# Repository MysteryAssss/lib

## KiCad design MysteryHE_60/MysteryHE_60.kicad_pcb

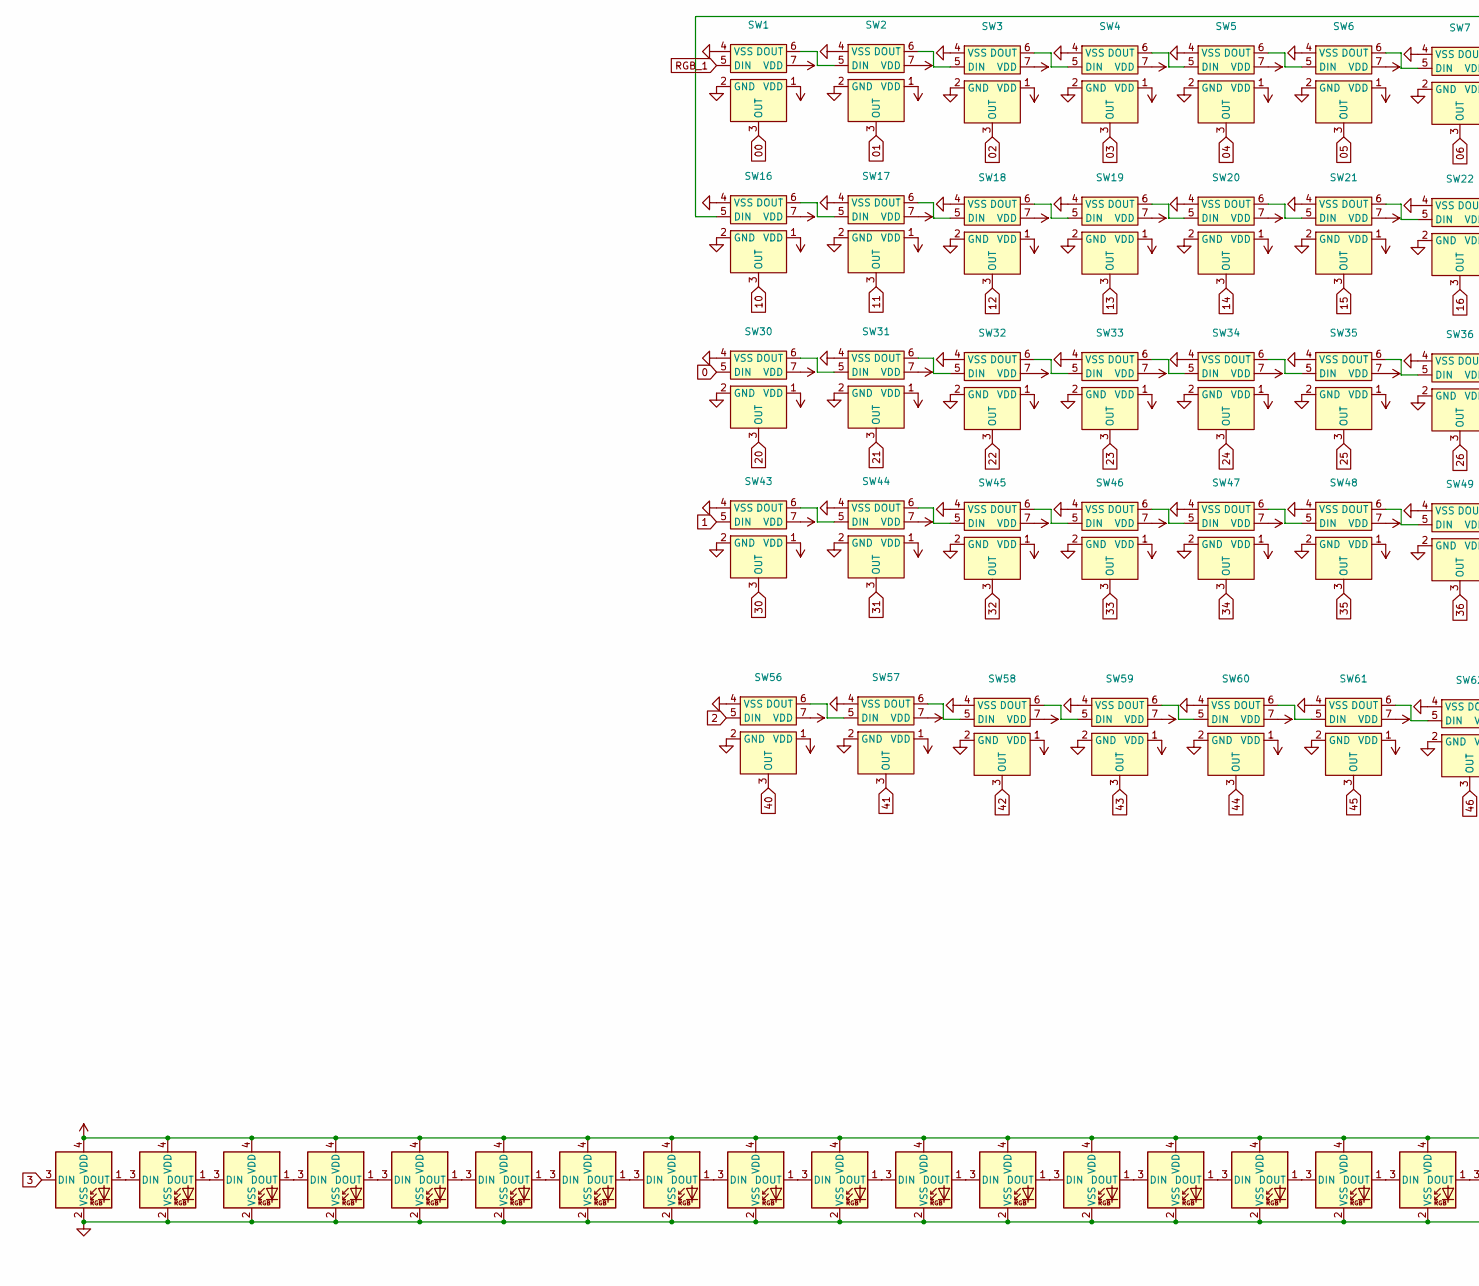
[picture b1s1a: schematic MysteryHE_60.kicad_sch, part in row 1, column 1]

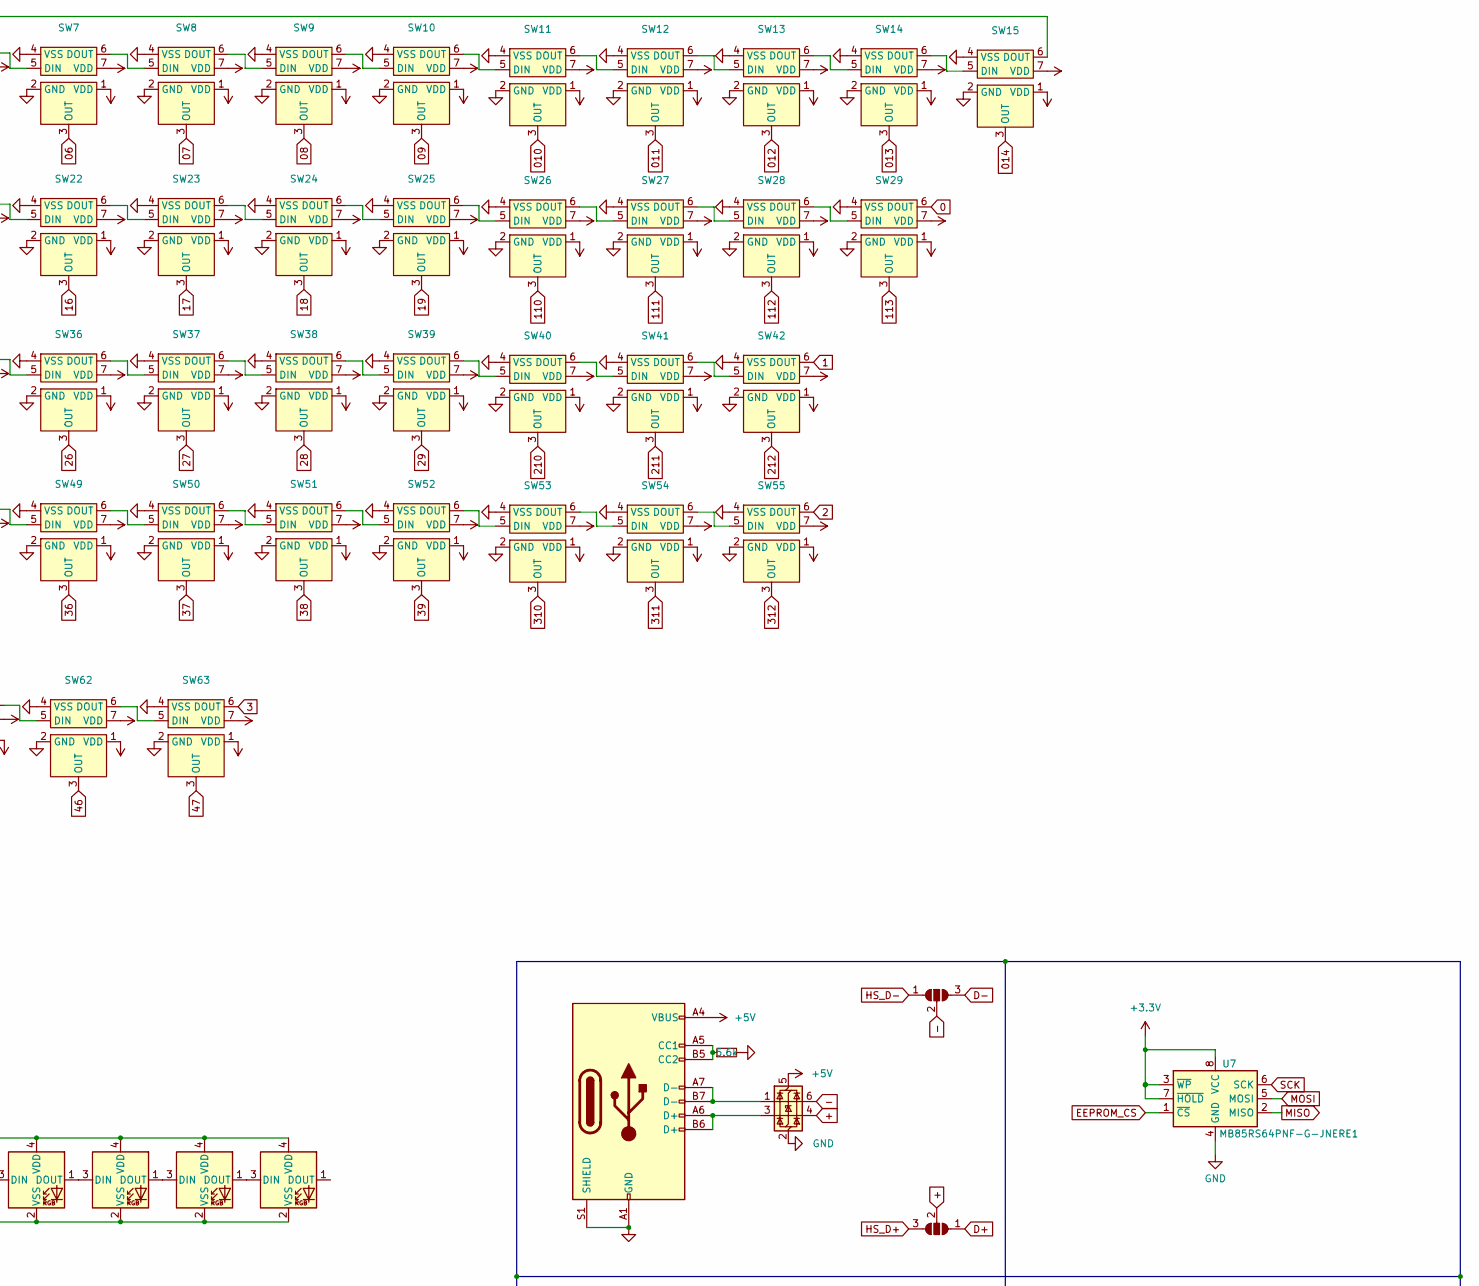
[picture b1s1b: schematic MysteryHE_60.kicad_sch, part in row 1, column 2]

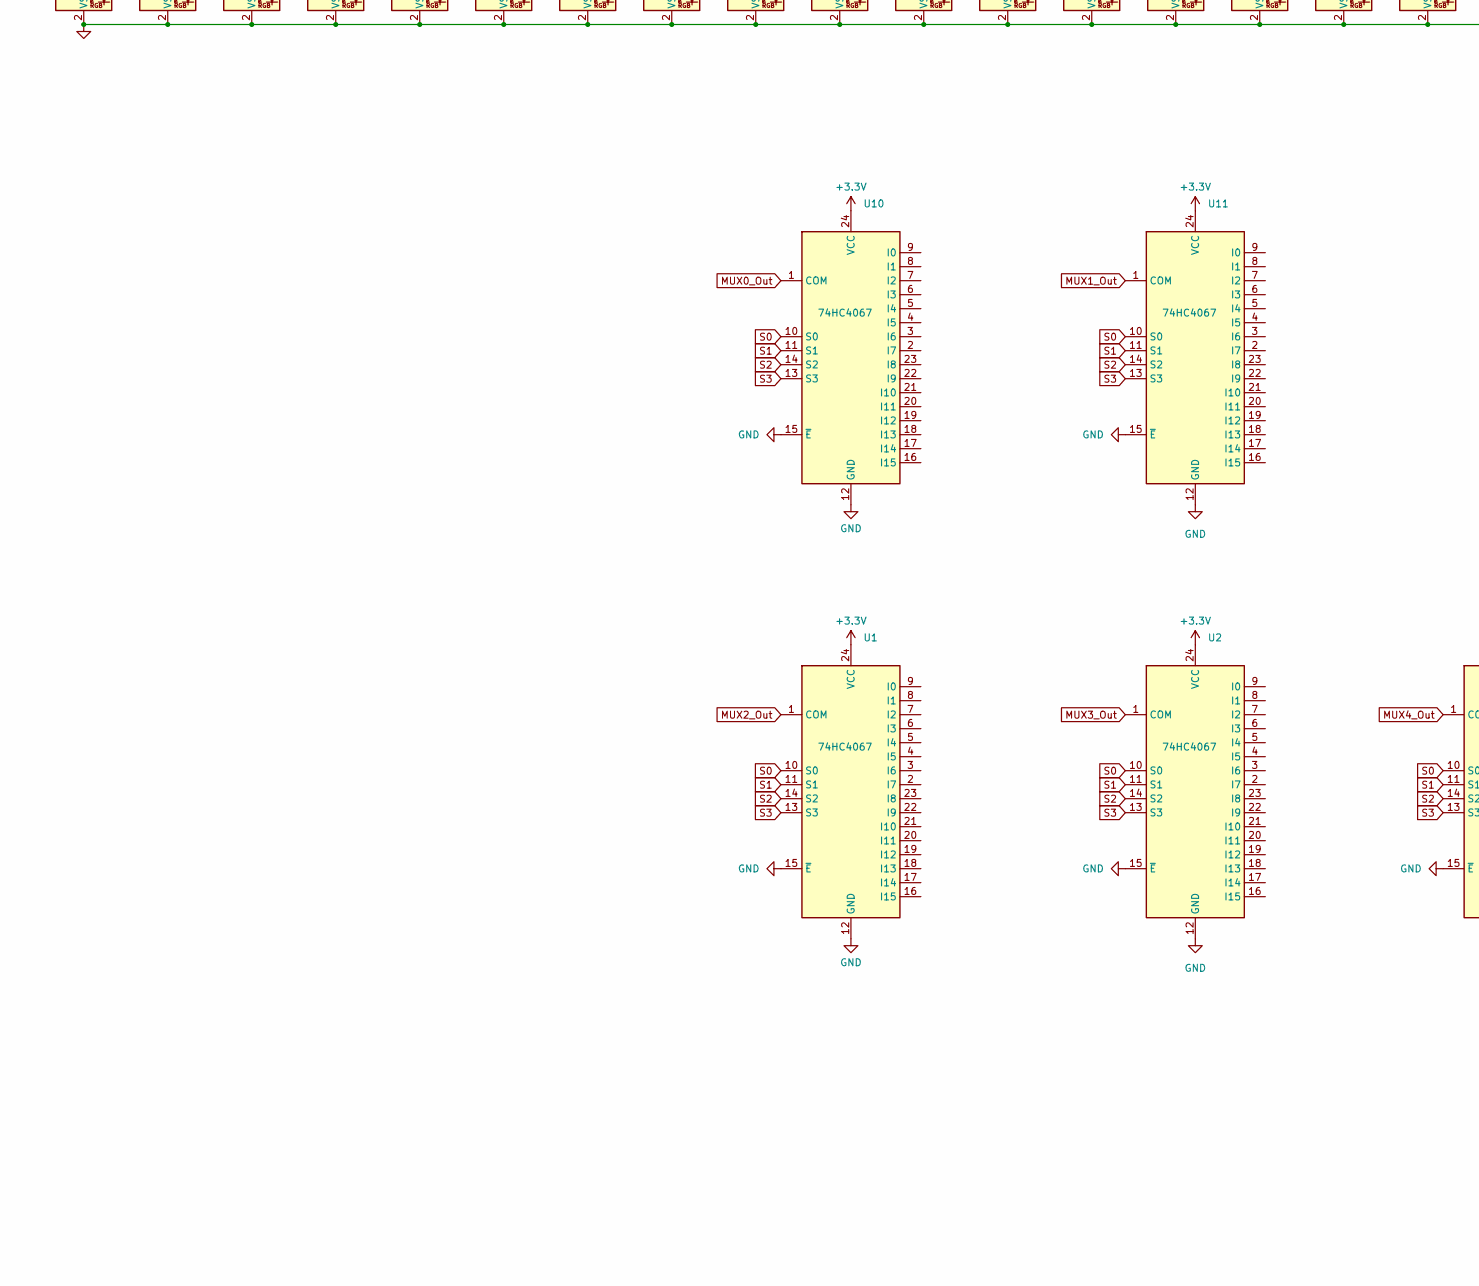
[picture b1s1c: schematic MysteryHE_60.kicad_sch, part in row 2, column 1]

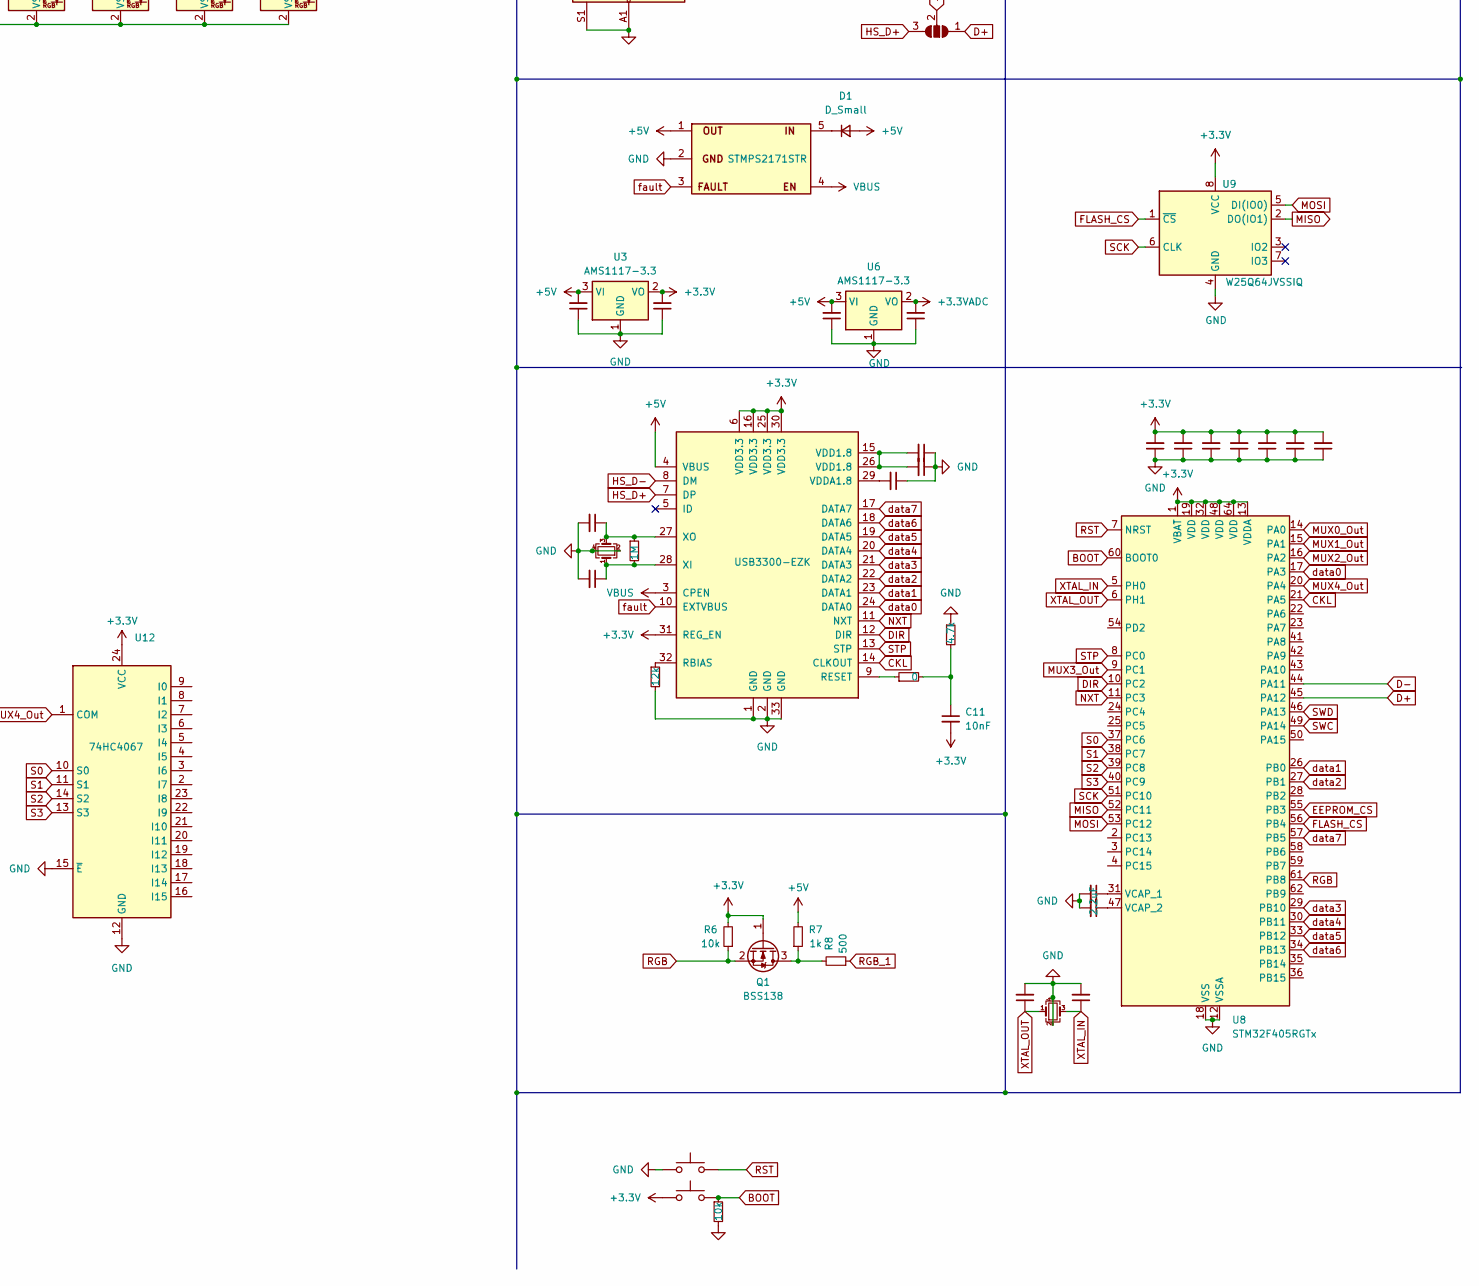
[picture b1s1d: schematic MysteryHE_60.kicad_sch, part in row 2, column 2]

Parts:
BOOT1: SW_Push; JST_EH_B2B-EH-A_1x02_P2.50mm_Vertical
C1, C2, C3, C5, C6, C8, C12, C15: 12pF; C_0603_1608Metric
C7, C9: 4.7uF; C_0603_1608Metric
C10: 1uF; C_0603_1608Metric
C11: 10nF; C_0603_1608Metric
C16, C17: 2.2uF; C_0603_1608Metric
C18, C19, C20, C21, C22, C23, C24: 0.1Uf; C_0603_1608Metric
D1: D_Small; D_SOD-123
Drgb1, Drgb2, Drgb3, Drgb4, Drgb5, Drgb6, Drgb7, Drgb8, Drgb9, Drgb10, Drgb11, Drgb12, Drgb13, Drgb14, Drgb15, Drgb16, Drgb17, Drgb18, Drgb19, Drgb20: WS2812B-2020; LED_WS2812B-2020_PLCC4_2.0x2.0mm
J1: STMPS2171STR; SOT-23-5
JP1, JP2: SolderJumper_3_Open; SW_SPDT_PCM12
Jd1: USB_C_Receptacle_USB2.0_14P; USB_C_Receptacle_G-Switch_GT-USB-7010ASV
Q1: BSS138; SOT-23
R1: 1M; R_0603_1608Metric
R3: 12k; R_0603_1608Metric
R4, R6: 10k; R_0603_1608Metric
R5: 5.6k; R_0603_1608Metric
R7: 1k; R_0603_1608Metric
R8: 500; R_0603_1608Metric
R9: 0; R_0603_1608Metric
R10: 4.7k; R_0603_1608Metric
RST1: SW_Push; JST_EH_B2B-EH-A_1x02_P2.50mm_Vertical
SW1, SW2, SW3, SW4, SW5, SW6, SW7, SW8, SW9, SW10, SW11, SW12, SW13, SW14, SW15, SW17, SW18, SW19, SW20, SW21, SW22, SW23, SW24, SW25, SW26, SW27, SW28, SW31, SW32, SW33, SW34, SW35, SW36, SW37, SW38, SW39, SW40, SW41, SW44, SW45, SW46, SW47, SW48, SW49, SW50, SW51, SW52, SW53, SW55, SW57, SW61: HE_1u RGB
SW16, SW29, SW56, SW58, SW60, SW62: HE_1.5u RGB
SW30, SW54: HE_1.75u RGB
SW42, SW43: HE_2.25u RGB
SW59: HE_7u Reversed RGB
SW63: HE_2u RGB
U1, U2, U10, U11, U12: 74HC4067; TSSOP-24_4.4x7.8mm_P0.65mm
U3, U6: AMS1117-3.3; SOT-223-3_TabPin2
U4: USB3300-EZK; QFN-32-1EP_5x5mm_P0.5mm_EP3.45x3.45mm
U5: USBLC6-2SC6; SOT-23-6
U7: MB85RS64PNF-G-JNERE1; SO-8_3.9x4.9mm_P1.27mm; LCSC C8741
U8: STM32F405RGTx; LQFP-64_10x10mm_P0.5mm
U9: W25Q64JVSSIQ; SOIC-8_5.23x5.23mm_P1.27mm; LCSC C179171
Y1: 24mhz; Crystal_SMD_3225-4Pin_3.2x2.5mm
Y2: 12mhz; Crystal_SMD_3225-4Pin_3.2x2.5mm

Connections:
0: SW29.6 (DOUT), SW30.5 (DIN)
00: SW1.3 (OUT)
1: SW42.6 (DOUT), SW43.5 (DIN)
01: SW2.3 (OUT)
02: SW3.3 (OUT)
2: SW55.6 (DOUT), SW56.5 (DIN)
3: Drgb20.3 (DIN), SW63.6 (DOUT)
03: SW4.3 (OUT)
04: SW5.3 (OUT)
05: SW6.3 (OUT)
06: SW7.3 (OUT)
07: SW8.3 (OUT)
08: SW9.3 (OUT)
09: SW10.3 (OUT)
10: SW16.3 (OUT)
010: SW11.3 (OUT)
011: SW12.3 (OUT)
11: SW17.3 (OUT)
012: SW13.3 (OUT)
12: SW18.3 (OUT)
013: SW14.3 (OUT)
13: SW19.3 (OUT)
14: SW20.3 (OUT)
014: SW15.3 (OUT)
15: SW21.3 (OUT)
16: SW22.3 (OUT)
17: SW23.3 (OUT)
18: SW24.3 (OUT)
19: SW25.3 (OUT)
20: SW30.3 (OUT)
21: SW31.3 (OUT)
22: SW32.3 (OUT)
23: SW33.3 (OUT)
24: SW34.3 (OUT)
25: SW35.3 (OUT)
26: SW36.3 (OUT)
27: SW37.3 (OUT)
28: SW38.3 (OUT)
29: SW39.3 (OUT)
30: SW43.3 (OUT)
31: SW44.3 (OUT)
32: SW45.3 (OUT)
33: SW46.3 (OUT)
34: SW47.3 (OUT)
35: SW48.3 (OUT)
36: SW49.3 (OUT)
37: SW50.3 (OUT)
38: SW51.3 (OUT)
39: SW52.3 (OUT)
40: SW56.3 (OUT)
41: SW57.3 (OUT)
42: SW58.3 (OUT)
43: SW59.3 (OUT)
44: SW60.3 (OUT)
45: SW61.3 (OUT)
46: SW62.3 (OUT)
47: SW63.3 (OUT)
110: SW26.3 (OUT)
111: SW27.3 (OUT)
112: SW28.3 (OUT)
113: SW29.3 (OUT)
210: SW40.3 (OUT)
211: SW41.3 (OUT)
212: SW42.3 (OUT)
310: SW53.3 (OUT)
311: SW54.3 (OUT)
312: SW55.3 (OUT)
+: JP2.2 (C), U5.4 (I/O2)
+3.3V: BOOT1.1, C5.2, C11.2, C18.2, C19.2, C20.2, C21.2, C22.2, C23.2, C24.2, Q1.1 (G), R6.2, U1.24 (VCC), U2.24 (VCC), U3.2 (VO), U4.6 (VDD3.3), U4.16 (VDD3.3), U4.25 (VDD3.3), U4.30 (VDD3.3), U4.31 (REG_EN), U7.3 (~WP), U7.7 (~HOLD), U7.8 (VCC), U8.1 (VBAT), U8.13 (VDDA), U8.19 (VDD), U8.32 (VDD), U8.48 (VDD), U8.64 (VDD), U9.8 (VCC), U10.24 (VCC), U11.24 (VCC), U12.24 (VCC)
+3.3VADC: C8.2, SW1.1 (VDD), SW2.1 (VDD), SW3.1 (VDD), SW4.1 (VDD), SW5.1 (VDD), SW6.1 (VDD), SW7.1 (VDD), SW8.1 (VDD), SW9.1 (VDD), SW10.1 (VDD), SW11.1 (VDD), SW12.1 (VDD), SW13.1 (VDD), SW14.1 (VDD), SW15.1 (VDD), SW16.1 (VDD), SW17.1 (VDD), SW18.1 (VDD), SW19.1 (VDD), SW20.1 (VDD), SW21.1 (VDD), SW22.1 (VDD), SW23.1 (VDD), SW24.1 (VDD), SW25.1 (VDD), SW26.1 (VDD), SW27.1 (VDD), SW28.1 (VDD), SW29.1 (VDD), SW30.1 (VDD), SW31.1 (VDD), SW32.1 (VDD), SW33.1 (VDD), SW34.1 (VDD), SW35.1 (VDD), SW36.1 (VDD), SW37.1 (VDD), SW38.1 (VDD), SW39.1 (VDD), SW40.1 (VDD), SW41.1 (VDD), SW42.1 (VDD), SW43.1 (VDD), SW44.1 (VDD), SW45.1 (VDD), SW46.1 (VDD), SW47.1 (VDD), SW48.1 (VDD), SW49.1 (VDD), SW50.1 (VDD), SW51.1 (VDD), SW52.1 (VDD), SW53.1 (VDD), SW54.1 (VDD), SW55.1 (VDD), SW56.1 (VDD), SW57.1 (VDD), SW58.1 (VDD), SW59.1 (VDD), SW60.1 (VDD), SW61.1 (VDD), SW62.1 (VDD), SW63.1 (VDD), U6.2 (VO)
+5V: C1.2, C6.2, D1.2 (A), Drgb1.4 (VDD), Drgb2.4 (VDD), Drgb3.4 (VDD), Drgb4.4 (VDD), Drgb5.4 (VDD), Drgb6.4 (VDD), Drgb7.4 (VDD), Drgb8.4 (VDD), Drgb9.4 (VDD), Drgb10.4 (VDD), Drgb11.4 (VDD), Drgb12.4 (VDD), Drgb13.4 (VDD), Drgb14.4 (VDD), Drgb15.4 (VDD), Drgb16.4 (VDD), Drgb17.4 (VDD), Drgb18.4 (VDD), Drgb19.4 (VDD), Drgb20.4 (VDD), J1.1, Jd1.A4 (VBUS), Jd1.A9 (VBUS), Jd1.B4 (VBUS), Jd1.B9 (VBUS), R7.2, SW1.7 (VDD), SW2.7 (VDD), SW3.7 (VDD), SW4.7 (VDD), SW5.7 (VDD), SW6.7 (VDD), SW7.7 (VDD), SW8.7 (VDD), SW9.7 (VDD), SW10.7 (VDD), SW11.7 (VDD), SW12.7 (VDD), SW13.7 (VDD), SW14.7 (VDD), SW15.7 (VDD), SW16.7 (VDD), SW17.7 (VDD), SW18.7 (VDD), SW19.7 (VDD), SW20.7 (VDD), SW21.7 (VDD), SW22.7 (VDD), SW23.7 (VDD), SW24.7 (VDD), SW25.7 (VDD), SW26.7 (VDD), SW27.7 (VDD), SW28.7 (VDD), SW29.7 (VDD), SW30.7 (VDD), SW31.7 (VDD), SW32.7 (VDD), SW33.7 (VDD), SW34.7 (VDD), SW35.7 (VDD), SW36.7 (VDD), SW37.7 (VDD), SW38.7 (VDD), SW39.7 (VDD), SW40.7 (VDD), SW41.7 (VDD), SW42.7 (VDD), SW43.7 (VDD), SW44.7 (VDD), SW45.7 (VDD), SW46.7 (VDD), SW47.7 (VDD), SW48.7 (VDD), SW49.7 (VDD), SW50.7 (VDD), SW51.7 (VDD), SW52.7 (VDD), SW53.7 (VDD), SW54.7 (VDD), SW55.7 (VDD), SW56.7 (VDD), SW57.7 (VDD), SW58.7 (VDD), SW59.7 (VDD), SW60.7 (VDD), SW61.7 (VDD), SW62.7 (VDD), SW63.7 (VDD), U3.3 (VI), U4.4 (VBUS), U5.5 (VBUS), U6.3 (VI)
-: JP1.2 (C), U5.6 (I/O1)
BOOT: BOOT1.2, R4.1, U8.60 (BOOT0)
CKL: U4.14 (CLKOUT), U8.21 (PA5)
D+: JP2.1 (A), U8.45 (PA12)
D-: JP1.3 (B), U8.44 (PA11)
DIR: U4.12 (DIR), U8.10 (PC2)
EEPROM_CS: U7.1 (~CS), U8.55 (PB3)
FLASH_CS: U8.56 (PB4), U9.1 (~CS)
GND: C1.1, C2.2, C3.2, C5.1, C6.1, C7.1, C8.1, C9.1, C10.1, C12.2, C15.2, C16.2, C17.2, C18.1, C19.1, C20.1, C21.1, C22.1, C23.1, C24.1, Drgb1.2 (VSS), Drgb2.2 (VSS), Drgb3.2 (VSS), Drgb4.2 (VSS), Drgb5.2 (VSS), Drgb6.2 (VSS), Drgb7.2 (VSS), Drgb8.2 (VSS), Drgb9.2 (VSS), Drgb10.2 (VSS), Drgb11.2 (VSS), Drgb12.2 (VSS), Drgb13.2 (VSS), Drgb14.2 (VSS), Drgb15.2 (VSS), Drgb16.2 (VSS), Drgb17.2 (VSS), Drgb18.2 (VSS), Drgb19.2 (VSS), Drgb20.2 (VSS), J1.2, Jd1.A1 (GND), Jd1.A12 (GND), Jd1.B1 (GND), Jd1.B12 (GND), Jd1.S1 (SHIELD), R3.2, R4.2, R5.2, R10.1, RST1.1, SW1.2 (GND), SW1.4 (VSS), SW2.2 (GND), SW2.4 (VSS), SW3.2 (GND), SW3.4 (VSS), SW4.2 (GND), SW4.4 (VSS), SW5.2 (GND), SW5.4 (VSS), SW6.2 (GND), SW6.4 (VSS), SW7.2 (GND), SW7.4 (VSS), SW8.2 (GND), SW8.4 (VSS), SW9.2 (GND), SW9.4 (VSS), SW10.2 (GND), SW10.4 (VSS), SW11.2 (GND), SW11.4 (VSS), SW12.2 (GND), SW12.4 (VSS), SW13.2 (GND), SW13.4 (VSS), SW14.2 (GND), SW14.4 (VSS), SW15.2 (GND), SW15.4 (VSS), SW16.2 (GND), SW16.4 (VSS), SW17.2 (GND), SW17.4 (VSS), SW18.2 (GND), SW18.4 (VSS), SW19.2 (GND), SW19.4 (VSS), SW20.2 (GND), SW20.4 (VSS), SW21.2 (GND), SW21.4 (VSS), SW22.2 (GND), SW22.4 (VSS), SW23.2 (GND), SW23.4 (VSS), SW24.2 (GND), SW24.4 (VSS), SW25.2 (GND), SW25.4 (VSS), SW26.2 (GND), SW26.4 (VSS), SW27.2 (GND), SW27.4 (VSS), SW28.2 (GND), SW28.4 (VSS), SW29.2 (GND), SW29.4 (VSS), SW30.2 (GND), SW30.4 (VSS), SW31.2 (GND), SW31.4 (VSS), SW32.2 (GND), SW32.4 (VSS), SW33.2 (GND), SW33.4 (VSS), SW34.2 (GND), SW34.4 (VSS), SW35.2 (GND), SW35.4 (VSS), SW36.2 (GND), SW36.4 (VSS), SW37.2 (GND), SW37.4 (VSS), SW38.2 (GND), SW38.4 (VSS), SW39.2 (GND), SW39.4 (VSS), SW40.2 (GND), SW40.4 (VSS), SW41.2 (GND), SW41.4 (VSS), SW42.2 (GND), SW42.4 (VSS), SW43.2 (GND), SW43.4 (VSS), SW44.2 (GND), SW44.4 (VSS), SW45.2 (GND), SW45.4 (VSS), SW46.2 (GND), SW46.4 (VSS), SW47.2 (GND), SW47.4 (VSS), SW48.2 (GND), SW48.4 (VSS), SW49.2 (GND), SW49.4 (VSS), SW50.2 (GND), SW50.4 (VSS), SW51.2 (GND), SW51.4 (VSS), SW52.2 (GND), SW52.4 (VSS), SW53.2 (GND), SW53.4 (VSS), SW54.2 (GND), SW54.4 (VSS), SW55.2 (GND), SW55.4 (VSS), SW56.2 (GND), SW56.4 (VSS), SW57.2 (GND), SW57.4 (VSS), SW58.2 (GND), SW58.4 (VSS), SW59.2 (GND), SW59.4 (VSS), SW60.2 (GND), SW60.4 (VSS), SW61.2 (GND), SW61.4 (VSS), SW62.2 (GND), SW62.4 (VSS), SW63.2 (GND), SW63.4 (VSS), U1.12 (GND), U1.15 (~E), U2.12 (GND), U2.15 (~E), U3.1 (GND), U4.1 (GND), U4.2 (GND), U4.33 (GND), U5.2 (GND), U6.1 (GND), U7.4 (GND), U8.12 (VSSA), U8.18 (VSS), U8.63 (VSS), U9.4 (GND), U10.12 (GND), U10.15 (~E), U11.12 (GND), U11.15 (~E), U12.12 (GND), U12.15 (~E), Y1.2, Y1.4, Y2.2, Y2.4
HS_D+: JP2.3 (B), U4.7 (DP)
HS_D-: JP1.1 (A), U4.8 (DM)
MISO: U7.2 (MISO), U8.52 (PC11), U9.2 (DO(IO1))
MOSI: U7.5 (MOSI), U8.53 (PC12), U9.5 (DI(IO0))
MUX0_Out: U8.14 (PA0), U10.1 (COM)
MUX1_Out: U8.15 (PA1), U11.1 (COM)
MUX2_Out: U1.1 (COM), U8.16 (PA2)
MUX3_Out: U2.1 (COM), U8.9 (PC1)
MUX4_Out: U8.20 (PA4), U12.1 (COM)
NXT: U4.11 (NXT), U8.11 (PC3)
unnamed: C9.2, C10.2, U4.15 (VDD1.8), U4.26 (VDD1.8)
unnamed: C11.1, R9.2, R10.2
unnamed: D1.1 (K), J1.5
unnamed: Drgb1.3 (DIN), Drgb20.1 (DOUT)
unnamed: Drgb1.1 (DOUT), Drgb2.3 (DIN)
unnamed: Drgb2.1 (DOUT), Drgb3.3 (DIN)
unnamed: Drgb3.1 (DOUT), Drgb4.3 (DIN)
unnamed: Drgb4.1 (DOUT), Drgb5.3 (DIN)
unnamed: Drgb5.1 (DOUT), Drgb6.3 (DIN)
unnamed: Drgb6.1 (DOUT), Drgb7.3 (DIN)
unnamed: Drgb7.1 (DOUT), Drgb8.3 (DIN)
unnamed: Drgb8.1 (DOUT), Drgb9.3 (DIN)
unnamed: Drgb9.1 (DOUT), Drgb10.3 (DIN)
unnamed: Drgb10.1 (DOUT), Drgb11.3 (DIN)
unnamed: Drgb11.1 (DOUT), Drgb12.3 (DIN)
unnamed: Drgb12.1 (DOUT), Drgb13.3 (DIN)
unnamed: Drgb13.1 (DOUT), Drgb14.3 (DIN)
unnamed: Drgb14.1 (DOUT), Drgb15.3 (DIN)
unnamed: Drgb15.1 (DOUT), Drgb16.3 (DIN)
unnamed: Drgb16.1 (DOUT), Drgb17.3 (DIN)
unnamed: Drgb17.1 (DOUT), Drgb18.3 (DIN)
unnamed: Drgb18.1 (DOUT), Drgb19.3 (DIN)
unnamed: Jd1.A5 (CC1), Jd1.B5 (CC2), R5.1
unnamed: Jd1.A6 (D+), Jd1.B6 (D+), U5.3 (I/O2)
unnamed: Jd1.A7 (D-), Jd1.B7 (D-), U5.1 (I/O1)
unnamed: Q1.3 (D), R7.1, R8.2
unnamed: SW1.6 (DOUT), SW2.5 (DIN)
unnamed: SW2.6 (DOUT), SW3.5 (DIN)
unnamed: SW3.6 (DOUT), SW4.5 (DIN)
unnamed: SW4.6 (DOUT), SW5.5 (DIN)
unnamed: SW5.6 (DOUT), SW6.5 (DIN)
unnamed: SW6.6 (DOUT), SW7.5 (DIN)
unnamed: SW7.6 (DOUT), SW8.5 (DIN)
unnamed: SW8.6 (DOUT), SW9.5 (DIN)
unnamed: SW9.6 (DOUT), SW10.5 (DIN)
unnamed: SW10.6 (DOUT), SW11.5 (DIN)
unnamed: SW11.6 (DOUT), SW12.5 (DIN)
unnamed: SW12.6 (DOUT), SW13.5 (DIN)
unnamed: SW13.6 (DOUT), SW14.5 (DIN)
unnamed: SW14.6 (DOUT), SW15.5 (DIN)
unnamed: SW15.6 (DOUT), SW16.5 (DIN)
unnamed: SW16.6 (DOUT), SW17.5 (DIN)
unnamed: SW17.6 (DOUT), SW18.5 (DIN)
unnamed: SW18.6 (DOUT), SW19.5 (DIN)
unnamed: SW19.6 (DOUT), SW20.5 (DIN)
unnamed: SW20.6 (DOUT), SW21.5 (DIN)
unnamed: SW21.6 (DOUT), SW22.5 (DIN)
unnamed: SW22.6 (DOUT), SW23.5 (DIN)
unnamed: SW23.6 (DOUT), SW24.5 (DIN)
unnamed: SW24.6 (DOUT), SW25.5 (DIN)
unnamed: SW25.6 (DOUT), SW26.5 (DIN)
unnamed: SW26.6 (DOUT), SW27.5 (DIN)
unnamed: SW27.6 (DOUT), SW28.5 (DIN)
unnamed: SW28.6 (DOUT), SW29.5 (DIN)
unnamed: SW30.6 (DOUT), SW31.5 (DIN)
unnamed: SW31.6 (DOUT), SW32.5 (DIN)
unnamed: SW32.6 (DOUT), SW33.5 (DIN)
unnamed: SW33.6 (DOUT), SW34.5 (DIN)
unnamed: SW34.6 (DOUT), SW35.5 (DIN)
unnamed: SW35.6 (DOUT), SW36.5 (DIN)
unnamed: SW36.6 (DOUT), SW37.5 (DIN)
unnamed: SW37.6 (DOUT), SW38.5 (DIN)
unnamed: SW38.6 (DOUT), SW39.5 (DIN)
unnamed: SW39.6 (DOUT), SW40.5 (DIN)
unnamed: SW40.6 (DOUT), SW41.5 (DIN)
unnamed: SW41.6 (DOUT), SW42.5 (DIN)
unnamed: SW43.6 (DOUT), SW44.5 (DIN)
unnamed: SW44.6 (DOUT), SW45.5 (DIN)
unnamed: SW45.6 (DOUT), SW46.5 (DIN)
unnamed: SW46.6 (DOUT), SW47.5 (DIN)
unnamed: SW47.6 (DOUT), SW48.5 (DIN)
unnamed: SW48.6 (DOUT), SW49.5 (DIN)
unnamed: SW49.6 (DOUT), SW50.5 (DIN)
unnamed: SW50.6 (DOUT), SW51.5 (DIN)
unnamed: SW51.6 (DOUT), SW52.5 (DIN)
unnamed: SW52.6 (DOUT), SW53.5 (DIN)
unnamed: SW53.6 (DOUT), SW54.5 (DIN)
unnamed: SW54.6 (DOUT), SW55.5 (DIN)
unnamed: SW56.6 (DOUT), SW57.5 (DIN)
unnamed: SW57.6 (DOUT), SW58.5 (DIN)
unnamed: SW58.6 (DOUT), SW59.5 (DIN)
unnamed: SW59.6 (DOUT), SW60.5 (DIN)
unnamed: SW60.6 (DOUT), SW61.5 (DIN)
unnamed: SW61.6 (DOUT), SW62.5 (DIN)
unnamed: SW62.6 (DOUT), SW63.5 (DIN)
unnamed: R3.1, U4.32 (RBIAS)
unnamed: R9.1, U4.9 (RESET)
unnamed: C7.2, U4.29 (VDDA1.8)
unnamed: C3.1, R1.2, U4.28 (XI), Y1.1
unnamed: C2.1, R1.1, U4.27 (XO), Y1.3
unnamed: C16.1, U8.31 (VCAP_1)
unnamed: C17.1, U8.47 (VCAP_2)
RGB: Q1.2 (S), R6.1, U8.61 (PB8)
RGB_1: R8.1, SW1.5 (DIN)
RST: RST1.2, U8.7 (NRST)
S0: U1.10 (S0), U2.10 (S0), U8.37 (PC6), U10.10 (S0), U11.10 (S0), U12.10 (S0)
S1: U1.11 (S1), U2.11 (S1), U8.38 (PC7), U10.11 (S1), U11.11 (S1), U12.11 (S1)
S2: U1.14 (S2), U2.14 (S2), U8.39 (PC8), U10.14 (S2), U11.14 (S2), U12.14 (S2)
S3: U1.13 (S3), U2.13 (S3), U8.40 (PC9), U10.13 (S3), U11.13 (S3), U12.13 (S3)
SCK: U7.6 (SCK), U8.51 (PC10), U9.6 (CLK)
STP: U4.13 (STP), U8.8 (PC0)
SWC: U8.49 (PA14)
SWD: U8.46 (PA13)
VBUS: J1.4, U4.3 (CPEN)
XTAL_IN: C15.1, U8.5 (PH0), Y2.3
XTAL_OUT: C12.1, U8.6 (PH1), Y2.1
data0: U4.24 (DATA0), U8.17 (PA3)
data1: U4.23 (DATA1), U8.26 (PB0)
data2: U4.22 (DATA2), U8.27 (PB1)
data3: U4.21 (DATA3), U8.29 (PB10)
data4: U4.20 (DATA4), U8.30 (PB11)
data5: U4.19 (DATA5), U8.33 (PB12)
data6: U4.18 (DATA6), U8.34 (PB13)
data7: U4.17 (DATA7), U8.57 (PB5)
fault: J1.3, U4.10 (EXTVBUS)

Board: 2 copper layers, 135 parts (72 on the bottom side), 140 nets, no tracks yet.
